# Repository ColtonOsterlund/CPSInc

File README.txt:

CHANGES TO MAKE: 
-remove remote origin
-Change heroku to pull from Server-Code in master branch
-.gitignore .env file in Server-Code - store environment variables in heroku instead

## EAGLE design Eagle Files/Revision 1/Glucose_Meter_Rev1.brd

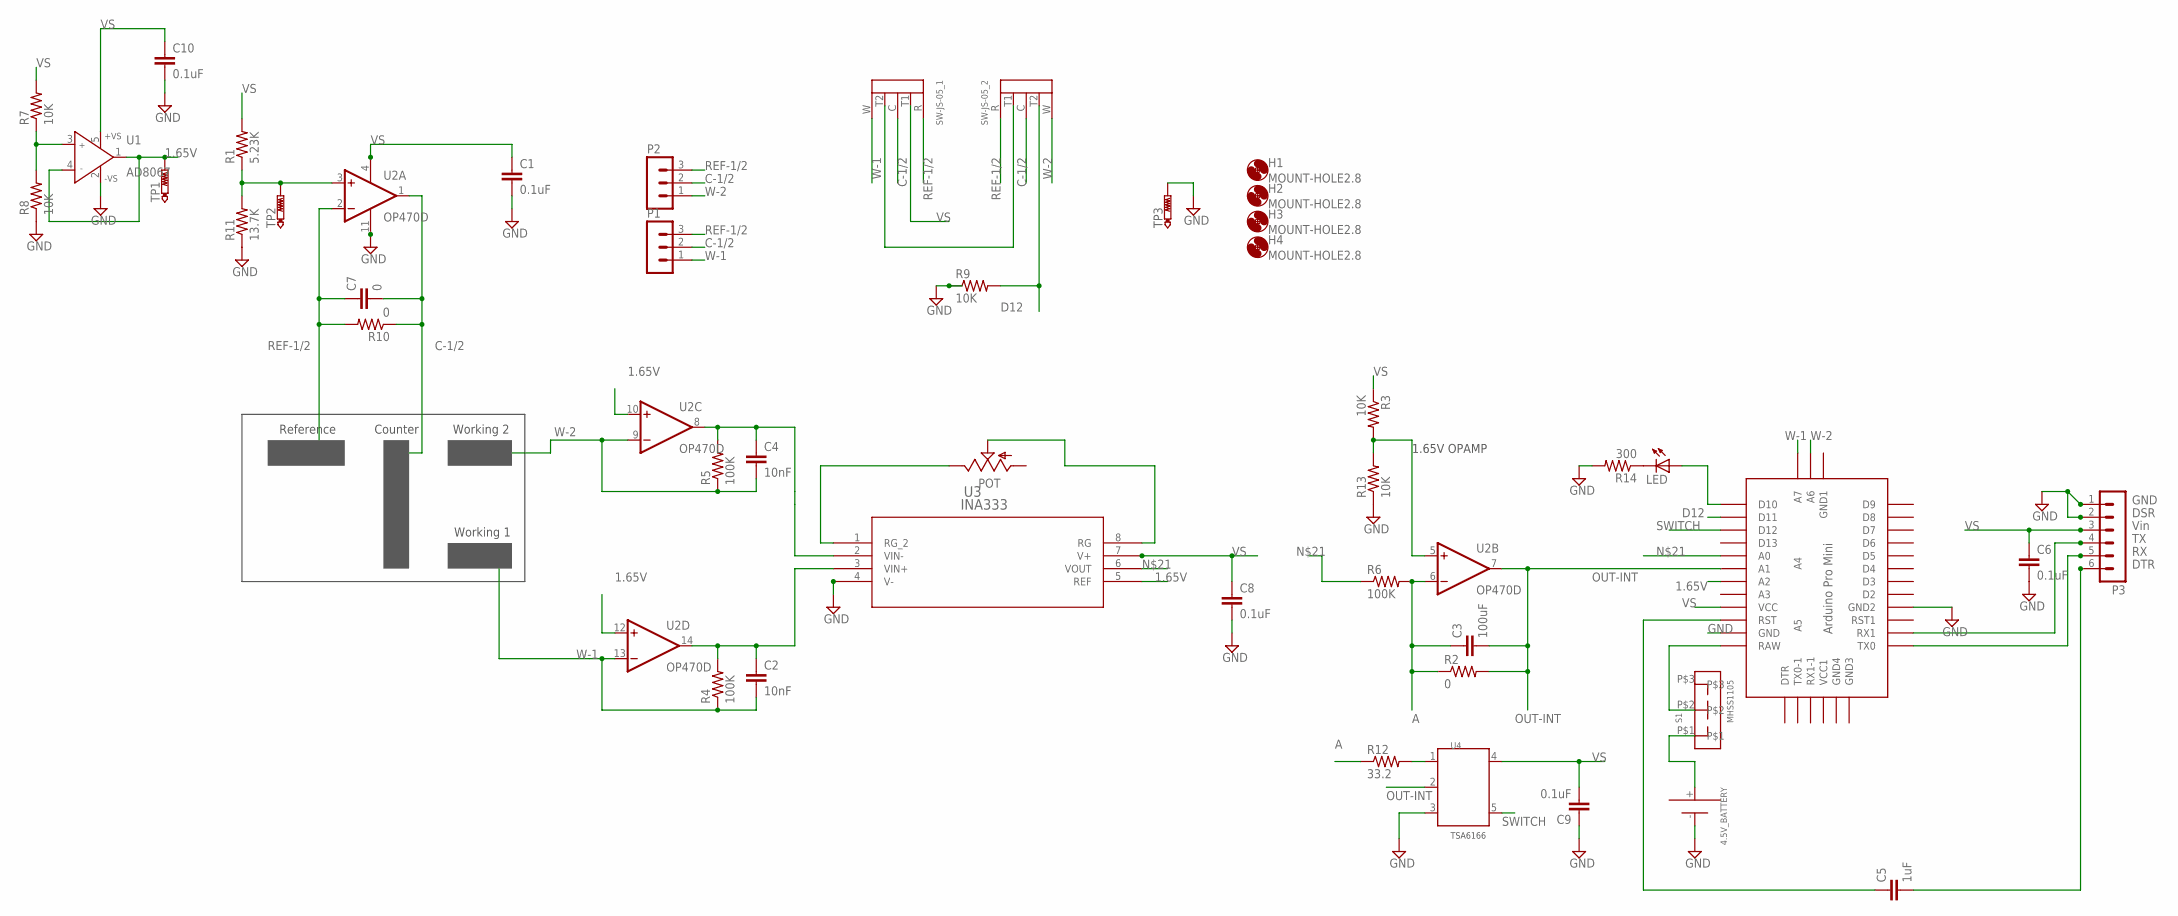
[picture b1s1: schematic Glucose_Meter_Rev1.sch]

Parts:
4.5V_BATTERY: BC3AAAPC
C1, C6, C8, C9, C10: 0.1uF; C0805
C2, C4: 10nF; C0805
C3: 100uF; C1210
C5: 1uF; C0805
C7: 0; C0805
H1, H2, H3, H4: MOUNT-HOLE2.8; 2,8
LED: LED3MM
P1, P2: MA03-1
P3: MA06-1
POT: TRIM_US-RJ9W; RJ9W
R1: 5.23K; R0805
R2, R10: 0; R0805
R3, R7, R8, R9, R13: 10K; R0805
R4, R5, R6: 100K; R0805
R11: 13.7K; R0805
R12: 33.2; R0805
R14: 300; R0805
S1: MHSS1105
SW-JS-05_1, SW-JS-05_2: SW-JS-05
TP1, TP2, TP3: PTR1PAD1-13; P1-13
U1: AD8067; SOT23-5
U2: OP470D; SO14
U3: INA333; DGK8
U4: TSA6166; SOT23-5
U$1: ABK-PRO-MINI

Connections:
1.65V: TP1.TP, U1.1 (OUT), U1.4 (IN-), U2.10 (+IN), U2.12 (+IN), U3.5 (REF), U$1.A2
4.5V_BATTERY: S1.P$2, U$1.RAW
A: C3.1, R2.1, R6.2, R12.1, U2.6 (-IN)
C-1/2: C7.2, P1.2, P2.2, R10.1, SW-JS-05_1.C, SW-JS-05_2.C, U2.1 (OUT)
D12: R9.2, SW-JS-05_2.T2, U$1.D11
GND: 4.5V_BATTERY.-, C1.2, C6.2, C8.2, C9.1, C10.2, P3.1, P3.2, R8.1, R9.1, R11.1, R13.1, R14.2, TP3.TP, U1.2 (-VS), U2.11 (V-), U3.4 (V-), U4.3 (GND), U$1.GND, U$1.GND1 (GND2)
N: SW-JS-05_1.T2, SW-JS-05_2.T1
unnamed: R12.2, U4.1 (A)
unnamed: R1.1, R11.2, TP2.TP, U2.3 (+IN)
unnamed: C4.1, R5.2, U2.8 (OUT), U3.2 (VIN-)
unnamed: LED.A, U$1.D10
unnamed: POT.E, U3.1 (RG_2)
unnamed: POT.S, U3.8 (RG)
unnamed: P3.4, U$1.RX1
unnamed: R7.1, R8.2, U1.3 (IN+)
unnamed: P3.5, U$1.TX0
unnamed: C5.2, P3.6
unnamed: C5.1, U$1.RST
unnamed: R3.2, R13.2, U2.5 (+IN)
unnamed: C2.1, R4.2, U2.14 (OUT), U3.3 (VIN+)
unnamed: 4.5V_BATTERY.+, S1.P$1
unnamed: LED.K (C), R14.1
unnamed: R6.1, U3.6 (VOUT), U$1.A0
OUT-INT: C3.2, R2.2, U2.7 (OUT), U4.2 (B), U$1.A1
REF-1/2: C7.1, P1.3, P2.3, R10.2, SW-JS-05_1.R, SW-JS-05_2.R, U2.2 (-IN)
SWITCH: U4.5 (ON/OFF), U$1.D12
VS: C1.1, C6.1, C8.1, C9.2, C10.1, P3.3, R1.2, R3.1, R7.2, SW-JS-05_1.T1, U1.5 (+VS), U2.4 (V+), U3.7 (V+), U4.4 (VS), U$1.VCC
W-1: C2.2, P1.1, R4.1, SW-JS-05_1.W, U2.13 (-IN), U$1.A7
W-2: C4.2, P2.1, R5.1, SW-JS-05_2.W, U2.9 (-IN), U$1.A6

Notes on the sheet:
GND
DSR
Vin
DTR
1.65V OPAMP
Reference
Counter
Working 1
Working 2

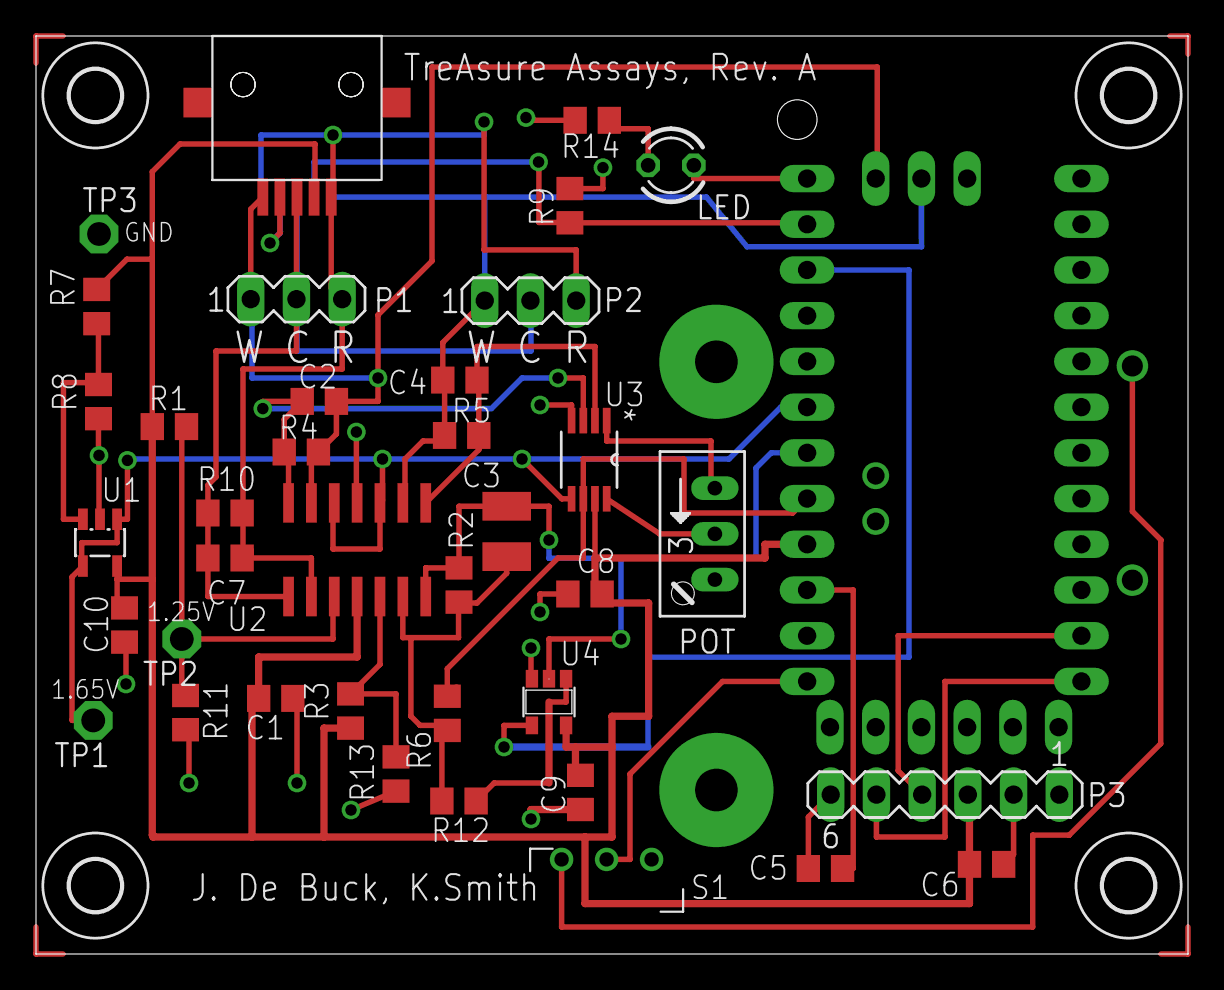
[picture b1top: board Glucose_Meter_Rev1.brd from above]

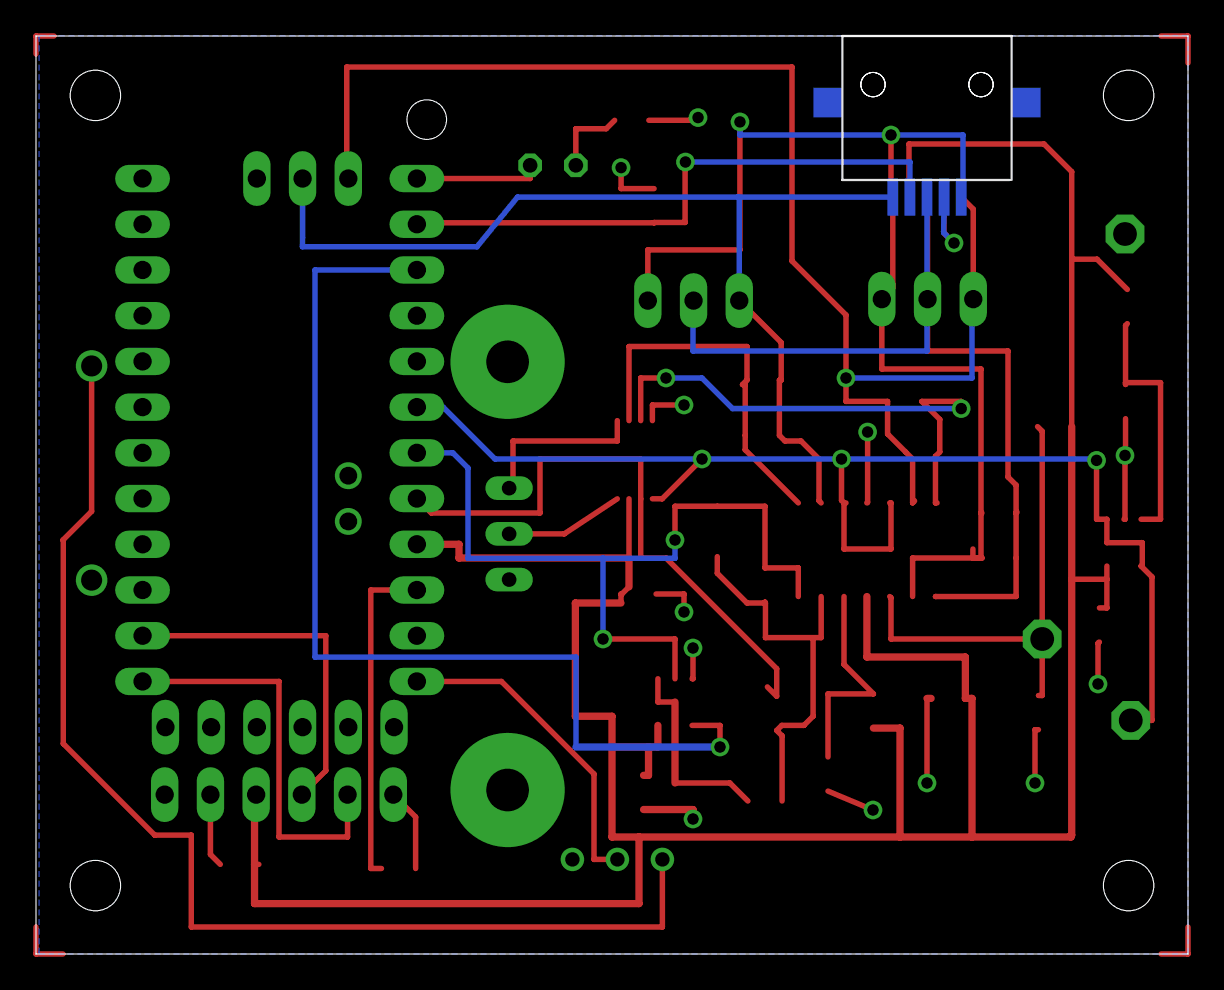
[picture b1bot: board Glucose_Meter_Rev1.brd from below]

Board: 2 copper layers, 64.0 x 51.0 mm, 45 parts (2 on the bottom side), 29 nets.

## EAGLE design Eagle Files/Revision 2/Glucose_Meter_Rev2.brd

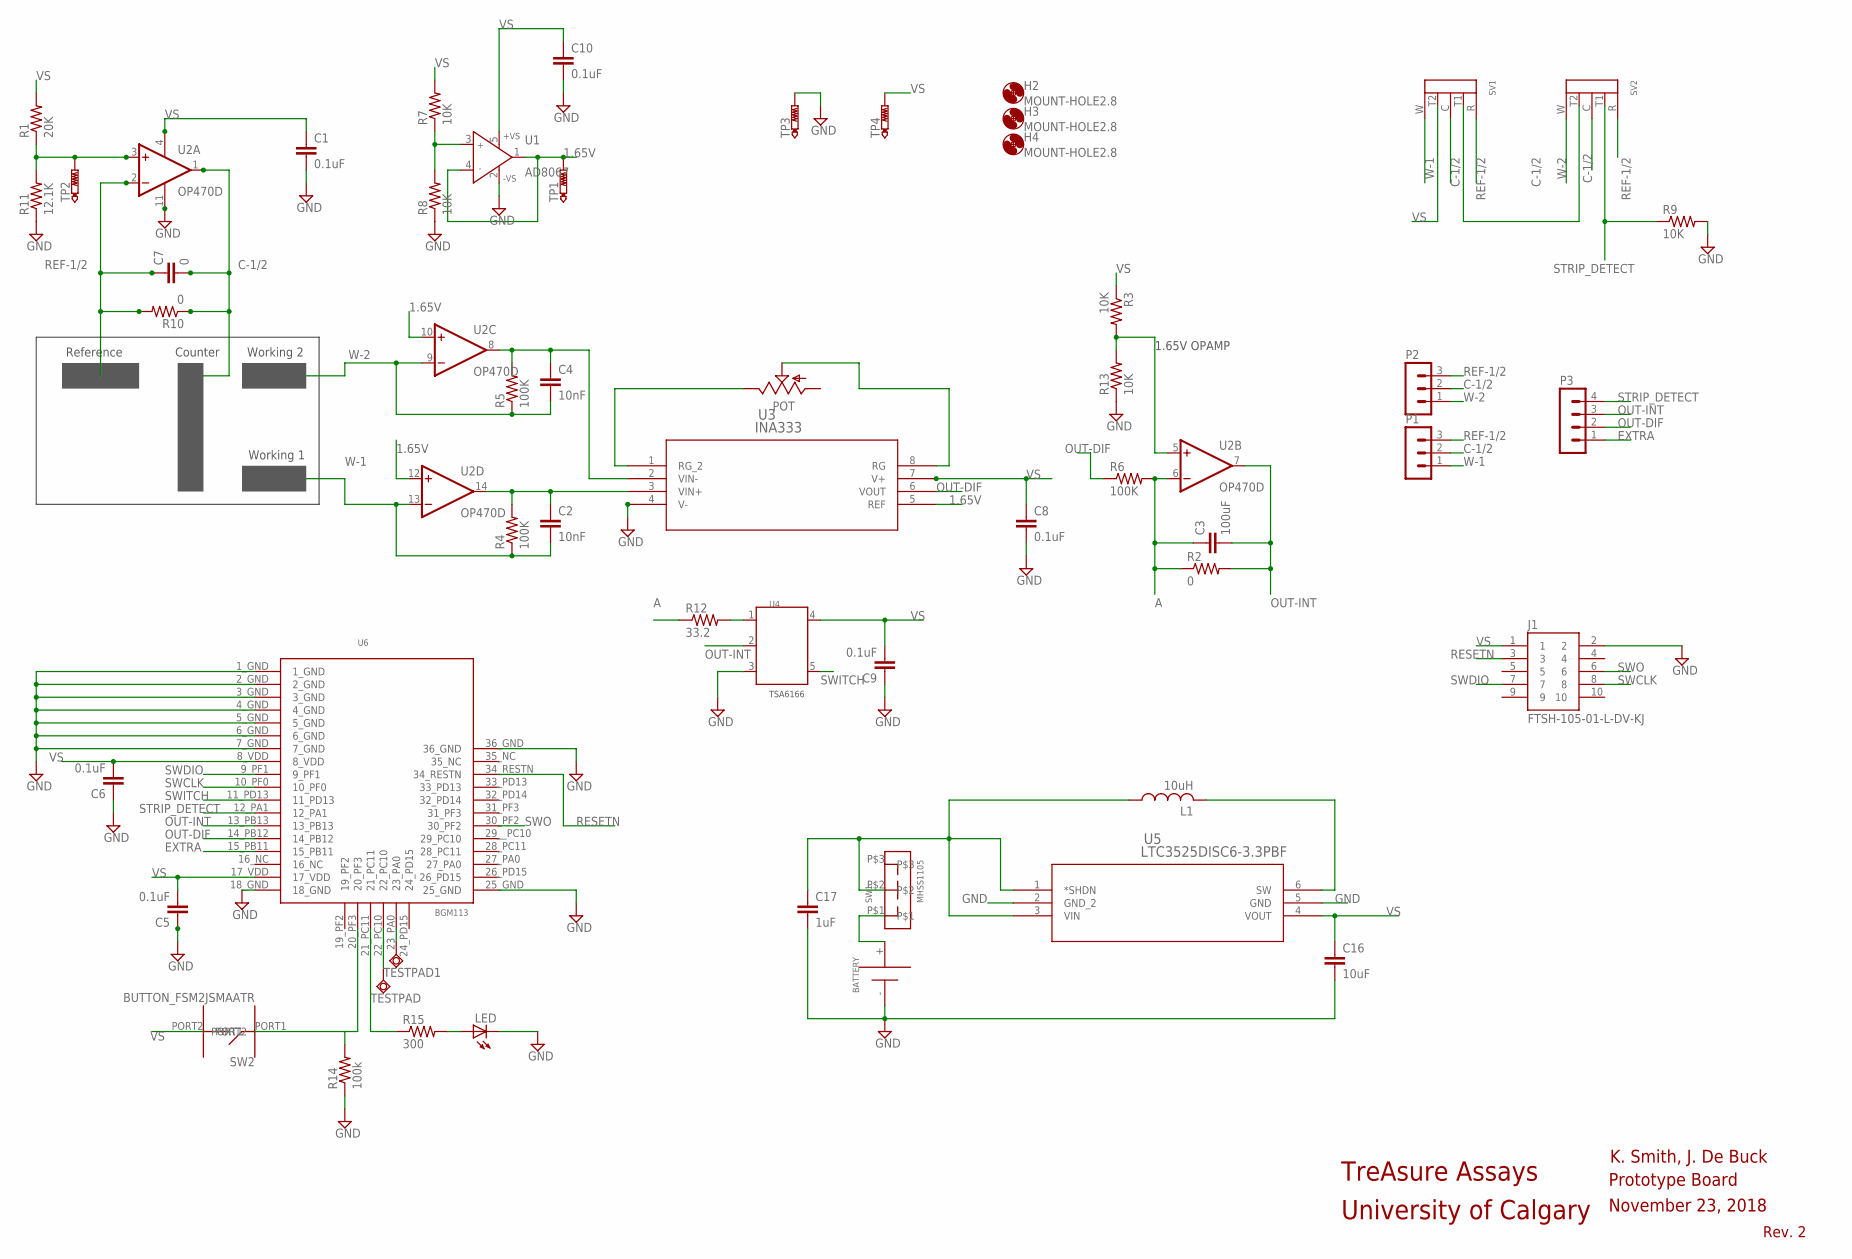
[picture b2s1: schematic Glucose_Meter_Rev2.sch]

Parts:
BATTERY: SMTU2032
C1, C5, C6, C8, C9, C10: 0.1uF; C0805
C2, C4: 10nF; C0805
C3: 100uF; C1210
C7: 0; C0805
C16: 10uF; C0805
C17: 1uF; C0805
H2, H3, H4: MOUNT-HOLE2.8; 2,8
J1: FTSH-105-01-L-DV-KJ; SAMTEC_FTSH-105-01-L-DV-K
L1: 10uH; L3225M
LED: LED3MM
P1, P2: MA03-1
P3: MA04-1
POT: TRIM_US-RJ9W; RJ9W
R1: 20K; R0805
R2, R10: 0; R0805
R3, R7, R8, R9, R13: 10K; R0805
R4, R5, R6: 100K; R0805
R11: 12.1K; R0805
R12: 33.2; R0805
R14: 100k; R0805
R15: 300; R0805
SV1, SV2: SW-JS-05
SW1: MHSS1105
SW2: BUTTON_FSM2JSMAATR
TESTPAD, TESTPAD1: TPSQTP06R; TP06R
TP1, TP2, TP3, TP4: PTR1PAD1-13; P1-13
U1: AD8067; SOT23-5
U2: OP470D; SO14
U3: INA333; DGK8
U4: TSA6166; SOT23-5
U5: LTC3525DISC6-3.3PBF; SC70-SC6
U6: BGM113

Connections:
1.65V: TP1.TP, U1.1 (OUT), U1.4 (IN-), U2.10 (+IN), U2.12 (+IN), U3.5 (REF)
3V_BATTERY1: C17.1, L1.1, SW1.P$2, U5.1 (*SHDN), U5.3 (VIN)
A: C3.1, R2.1, R6.2, R12.1, U2.6 (-IN)
C-1/2: C7.2, P1.2, P2.2, R10.1, SV1.C, SV2.C, U2.1 (OUT)
EXTRA: P3.1, U6.15_PB11
GND: BATTERY.-, C1.2, C5.1, C6.1, C8.2, C9.1, C10.2, C16.2, C17.2, J1.2, LED.K (C), R8.1, R9.2, R11.1, R13.1, R14.1, TP3.TP, U1.2 (-VS), U2.11 (V-), U3.4 (V-), U4.3 (GND), U5.2 (GND_2), U5.5 (GND), U6.1_GND, U6.2_GND, U6.3_GND, U6.4_GND, U6.5_GND, U6.6_GND, U6.7_GND, U6.18_GND, U6.25_GND, U6.36_GND
unnamed: R12.2, U4.1 (A)
unnamed: R1.1, R11.2, TP2.TP, U2.3 (+IN)
unnamed: BATTERY.+, SW1.P$1
unnamed: L1.2, U5.6 (SW)
unnamed: C4.1, R5.2, U2.8 (OUT), U3.2 (VIN-)
unnamed: R14.2, SW2.PORT1, U6.20_PF3
unnamed: POT.E, U3.1 (RG_2)
unnamed: POT.S, U3.8 (RG)
unnamed: LED.A, R15.2
unnamed: R15.1, U6.21_PC11
unnamed: R7.1, R8.2, U1.3 (IN+)
unnamed: SV1.T1, SV2.T2
unnamed: R3.2, R13.2, U2.5 (+IN)
unnamed: C2.1, R4.2, U2.14 (OUT), U3.3 (VIN+)
unnamed: TESTPAD.TP, U6.22_PC10
unnamed: TESTPAD1.TP, U6.23_PA0
OUT-DIF: P3.2, R6.1, U3.6 (VOUT), U6.14_PB12
OUT-INT: C3.2, P3.3, R2.2, U2.7 (OUT), U4.2 (B), U6.13_PB13
REF-1/2: C7.1, P1.3, P2.3, R10.2, SV1.R, SV2.R, U2.2 (-IN)
RESETN: J1.3, U6.34_RESTN
STRIP_DETECT: P3.4, R9.1, SV2.T1, U6.12_PA1
SWCLK: J1.8, U6.10_PF0
SWDIO: J1.7, U6.9_PF1
SWITCH: U4.5 (ON/OFF), U6.11_PD13
SWO: J1.6, U6.30_PF2
VS: C1.1, C5.2, C6.2, C8.1, C9.2, C10.1, C16.1, J1.1, R1.2, R3.1, R7.2, SV1.T2, SW2.PORT2, TP4.TP, U1.5 (+VS), U2.4 (V+), U3.7 (V+), U4.4 (VS), U5.4 (VOUT), U6.8_VDD, U6.17_VDD
W-1: C2.2, P1.1, R4.1, SV1.W, U2.13 (-IN)
W-2: C4.2, P2.1, R5.1, SV2.W, U2.9 (-IN)

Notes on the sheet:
1.65V OPAMP
Reference
Working 1
Working 2
Counter
TreAsure Assays
Prototype Board
Rev. 2
November 23, 2018
K. Smith, J. De Buck
University of Calgary

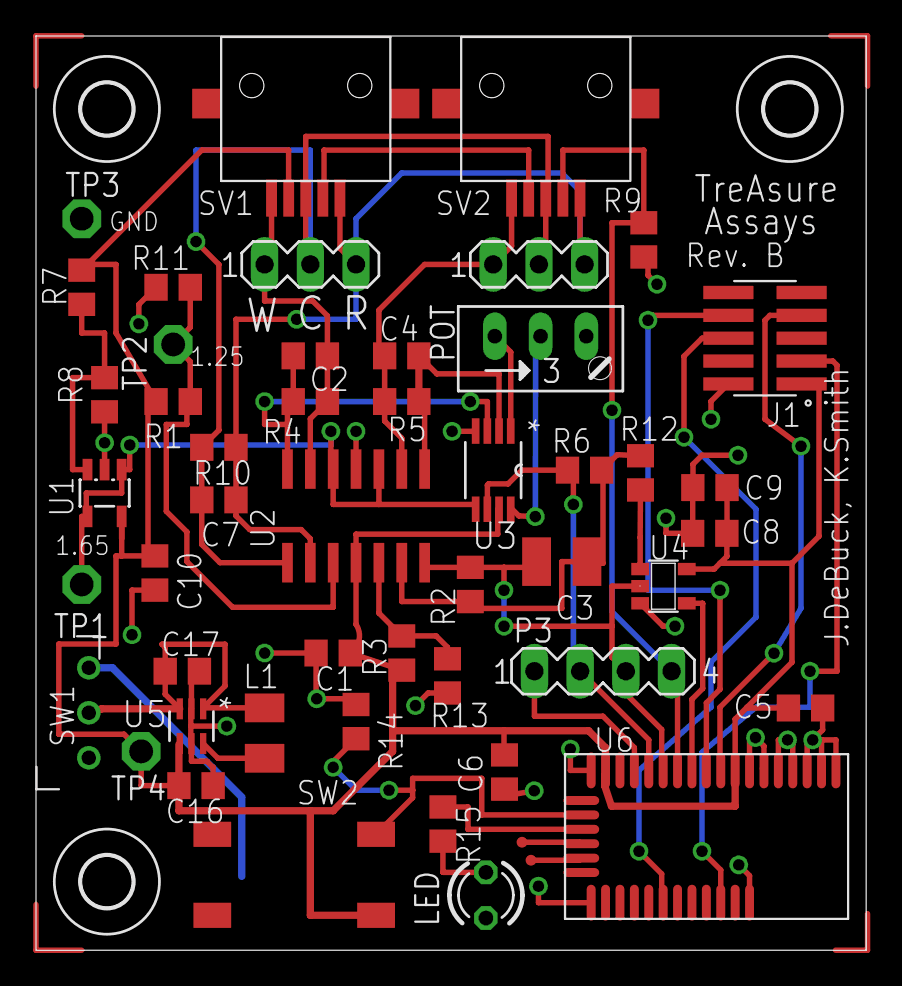
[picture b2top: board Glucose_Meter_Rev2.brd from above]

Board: 2 copper layers, 46.1 x 50.8 mm, 54 parts (1 on the bottom side), 34 nets.

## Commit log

2019-07-09 First commit to new repository - taking over from CPSInc. Previous repository
2019-07-10 Advancements on graphing selected results for cow feature
2019-07-11 added apple data encryption
2019-07-12 Wasn't saving data properly - bug fixed
2019-07-17 light updates
2019-07-17 Changed to EncryptedValueTransformer, changed int16 to NSNumber (still stored as an int16 but can now be turned to NSData)
2019-07-17 core data heavyweight migration between versions 1 and 2 set up
2019-07-18 notifications & incubation timer
2019-07-19 timer updates
2019-07-23 Basic Updates
2019-07-30 Login Features
2019-08-05 immunoglobulin test
2019-08-05 changed immunoglobulin equation
2019-08-07 fixed issue where ui didnt udate before pausing for non-zero value in immunoglobulins test
2019-08-19 threading for continuous test - many bug fixes
2019-08-21 bug fixes
2019-08-21 test commit
2019-08-21 cleaning up files
2019-08-21 uodate
2019-08-21 adding device BGM113 cODE
2019-08-28 changing development sign key file name so that repository can be cloned on windows
2019-08-28 adding server code
2019-08-28 setting up heroku auto deployment from subfolder
2019-08-28 Adding old files from Katrin
2019-08-29 added some commetns
2020-05-04 Adding Android Studio files for Android version of app
2020-05-05 adding pictures
2020-05-05 main page almost complete
2020-05-05 transitions from main page
2020-05-05 adding instructions activity file
2020-05-07 testing git
2020-05-07 reverting git test
2020-05-07 removing server code - now part of CPSIncBackend repository
2020-05-25 adding code to test hardware for new device in Simplicity Studio folder
2020-05-25 reorganizing simplicity studio code directory
2020-06-03 adding changes - siri working - still needs some work
2020-06-03 commiting changes
2020-06-03 changing pod file
2020-06-03 changing podfile
2020-06-03 removign intents file
2020-06-03 podfile change
2020-06-03 downloaded buy-sdk
2020-06-09 added store page, working - need to add checkout and payment features still. Problem with backend where all passwords work to login needs to be fixed
2020-06-11 editing timer interrupts for bgm113 temp sensor and motor control
2020-06-11 uncommenting timer interrupt for temp sensor, changing motor state control function
2020-06-29 shopify store
2020-07-02 changing Simplicity Studio workspace to version from August 2019 as that was the last version that StripDetectVoltage works, not many changes have been made since then
2020-07-02 version history change to simplicity studio to old version
2020-07-28 adding temp sensor, motor control and battery control pins to code for testing at DI
2020-08-04 reverting back to last working app.c file
2020-08-04 changed code so that you are able to test without having to connect device. Make sure to read comments thouroughly throughout
2020-08-05 debugging 0mV integrated voltage during testing
2020-08-11 update 3.0 on app store
2020-08-11 debugging
2020-08-11 dynamic innovation bug testing fix
2020-08-25 adding files for Yong - branch off from here for Yongs testing
2020-08-25 backing up files
2020-08-25 changing testing time from 30s to 8s
2020-08-25 fixing all LLC bugs
2020-08-26 fixing on yong compiter
2020-10-11 submitted new version to app store - fresh upload to fix the old app
2020-10-21 bug fixing - app store bug
2020-10-27 debugging App store bug
2020-12-03 Temperature and battery voltages send to GATT DB
2020-12-03 Unsaved changes from soc-empty_3.isc
2021-01-28 Adding support for heater pad to turn on when test starting and off when test finished
2021-01-28 Adding feature to make test wait for device to reach 27C before starting test
2021-01-29 most recent working device code with working heater pad
2021-02-05 Updates to testing workflow from working with travis
2021-02-05 need to commit to change branches
2021-02-05 adding device id characteristic
2021-02-07 Code working with two new devices dropped off from travis today
2021-02-07 some updates to code to clean up runTest workflow and take out unnecessary print statements and debugging queues on the app
2021-03-10 Added battery level detection when starting tests
2021-03-28 Adding ROI web slider tool
2021-03-30 Adding fields to cow object so that you can pull added data from database
2021-04-03 Moved battery and temperature calibration to the app side
2021-04-03 tempcommit
2021-04-13 iOS Updated Code
2021-06-02 Changing test timer to read voltages to 0.5s from 0.2s
2021-08-18 Updated App code
2021-08-24 App updates
2021-08-25 Changing singlestriptestviewcontroller
2021-08-25 Un hardcoding the temp and voltage values
2021-09-08 changes and bug fixes to singleStripTest for new test workflow
2021-09-09 adding changes from yesterday - fixing timer inconsistancies by invalidating test timer prior to creating a new one at the start of each test
2021-10-12 Changing admin privileges to be handled by an admin flag in the database
2021-11-08 changing default equation parameters
2021-11-16 Adding patch to be able to save quick tests to cow after test is taken
2021-11-16 adding filtering to cow list when selecting to save
